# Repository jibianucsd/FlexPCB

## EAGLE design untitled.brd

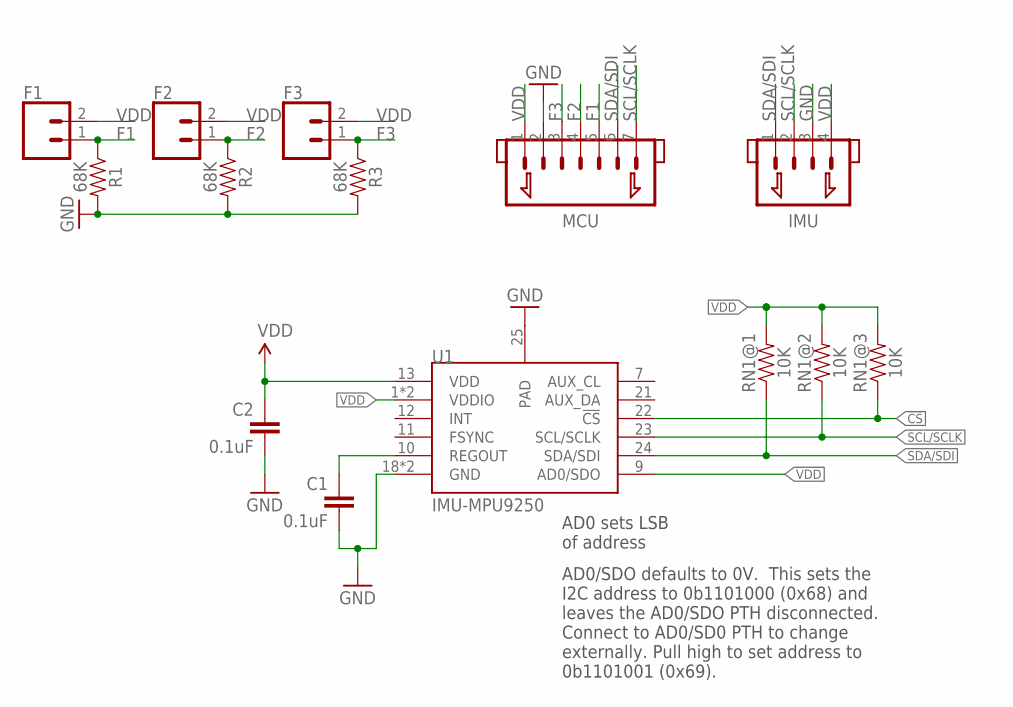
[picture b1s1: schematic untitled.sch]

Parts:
C1, C2: 0.1uF; 0603-CAP
F1, F2, F3: CONN_02LOCK_LONGPADS; 1X02_LOCK_LONGPADS
IMU: JST_1.25_4P; JST1.25_4P
MCU: JST_1.25_7P; JST1.25_7P
R1, R2, R3: 68K; 0603
RN1: 10K; RESCAF80P320X160X60-8N
U1: IMU-MPU9250; LEAD-QFN24

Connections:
!CS: RN1.3 (1), U1.22 (!CS)
F1: F1.1, MCU.5, R1.1
F2: F2.1, MCU.4, R2.1
F3: F3.1, MCU.3, R3.1
GND: C1.2, C2.2, IMU.3, MCU.2, R1.2, R2.2, R3.2, U1.18 (GND), U1.20 (GND), U1.25 (PAD)
REGOUT: C1.1, U1.10 (REGOUT)
SCL/SCLK: IMU.2, MCU.7, RN1.2 (1), U1.23 (SCL/SCLK)
SDA/SDI: IMU.1, MCU.6, RN1.1, U1.24 (SDA/SDI)
VDD: C2.1, F1.2, F2.2, F3.2, IMU.4, MCU.1, RN1.6 (2), RN1.7 (2), RN1.8 (2), U1.1 (VDDIO), U1.8 (VDDIO), U1.9 (AD0/SDO), U1.13 (VDD)

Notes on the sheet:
AD0/SDO defaults to 0V. This sets the I2C address to 0b1101000 (0x68) and leaves the AD0/SDO PTH disconnected. Connect to AD0/SD0 PTH to change externally. Pull high to set address to 0b1101001 (0x69).
AD0 sets LSB of address

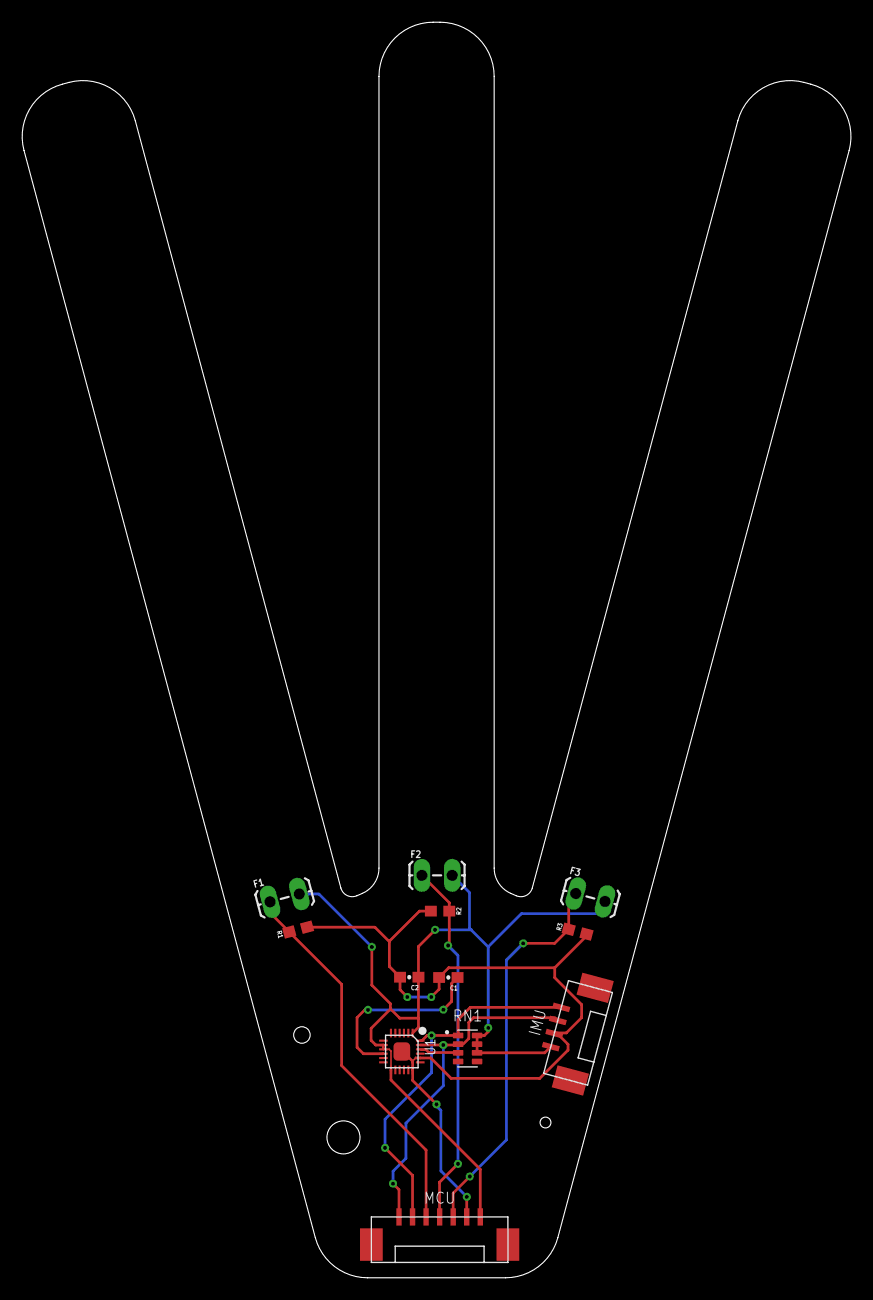
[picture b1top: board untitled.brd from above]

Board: 2 copper layers, 76.5 x 115.9 mm, 12 parts (0 on the bottom side), 9 nets.

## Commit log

2021-12-01 init

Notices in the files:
parts and their libraries:
SparkFun-Capacitors: Licensing: Creative Commons ShareAlike 4.0 International - https://creativecommons.org/licenses/by-sa/4.0
